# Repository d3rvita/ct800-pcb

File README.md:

# CT800-PCB

In order to become familiar with KiCAD and making something useful at the same time I started this project. The goal was to develop a PCB for the CT800 to ease the build-up. The CT800 is a dedicated chess computer made by Rasmus Althoff. It is very well documented, take a look at its homepage [www.ct800.net](https://www.ct800.net "CT800 Homepage") for detailed info. 

The developed PCB consists entirely of THT components except one SMD transistor, due to better availability of 3.3V logic level devices. Soldering SMD parts isn’t easy especially packages like LQFP64 with 0.5mm pitch, therefore the Olimex board was kept in this design. The CT800 was extended by some interfaces (RS232, Bluetooth, WLAN) for future use. The power supply was amended a bit too.

CAD files of appropriate panels for housings are also included in this project. There are two versions:

* the Spartan one consists of front and back panel which are bolted to the PCB by studs
* the Classic one consists of just a front panel for the housing used by Rasmus (Axxatronic BIM1006-BLK/PG or BIM1006-GY/PG)

These panels are intended to be transparent, hence there are no holes for display and LEDs. Due to transparency there is no need for additional button labels.

## Project Data

* __CT800_PCB__ directory contains the KiCAD project including project specific libs and footprints as well gerber files for PCB production

* __CT800_PANEL__ directory contains panels (in KiCAD layout and SVG formats) for different housings

* __gen_panel_acrylic.py__ Python script for generating panel layouts from PCB layout

* __bom.txt__ lists the bill of material, mounting material for panels not included (M3x8mm / M3x25mm studs, washers, bolts...)

## Power Supply

Depending on assembly the CT800 can be powered by different sources: 

* by a 5V source on the USB-A connector 
* by power adopter or external battery on the barrel jack
	* 8-12VDC if the 7805 voltage regulator is used 
	* 4-12VDC if the Pololu S9V11F5 is used
* by internal battery if a switch is used

The USB-B connector on the Olimex board is not intended for powering the CT800 but for USB devices like a sensor chessboard. So __don’t feed the CT800 via USB-B connector.__

__Don’t provide power from multiple sources simultaneously to the CT800 in general. This could lead to side effects or even damage!__

In order to feed the CT800 by low voltage power supply down to 4VDC  (e.g. battery) equip the PCB with the Pololu S9V11F5 voltage regulator (or similar 5V buck/boost converter) instead of the 7805. In this context replacing the 1N4007 diode by a Schottky type (e.g. 1N5818, SB130) is recommended for higher efficiency.

The CT800 firmware provides voltage monitoring for four NiMH (or alkaline) cells connected in serial, in order to protect rechargeable batteries from deep discharge. This only makes sense in conjunction with the Pololu regulator. Dispense with this monitoring eases the build-up, so omit it unless you really need it. To do so, omit the voltage divider components (R2, R3 and C1), instead connect the R2 pad next to C1 to 3.3V (red wire on ct800_spartan_bottom.jpg).

A power switch is not provided on the PCB but can be connected easily to PWR and USB_SEL pads.

### Operating Without Power Switch

The CT800 is immediately powered by plugging a 5V supply to the USB-A connector or a “wide range” power source to the barrel jack (8-12VDC or 4-12VDC depending on the used 5V regulator).

If battery monitoring is active (thus the Pololu is used), the USB power has to be redirected to 5V regulator’s input via the USB_SEL jumper: disrupt the connection on top side between the upper two pads and short-circuit the lower two. Otherwise powering via USB will result in “low batteries” error message. Because of this redirection the power adopter (or battery) is directly connected to the USB power supply. __Despite the fuses, this easily lead to damage in case two power sources are used simultaneously!__ Therefore use a switch instead or dispense with battery monitoring.

### Operating With Power Switch

Without battery monitoring a 2x3 pin toggle switch is sufficient to switch between USB-A and barrel jack supply. An external battery can still be used on the barrel jack. If internal battery is desired a 1x4 rotary switch is recommended for supply selection. Wire the switch as shown in the picture below, don’t forget to disrupt the red marked traces on the PCB.

Many other switch configurations are possible. Whatever you choose, ensure power sources are never short circuit!

## PCB Assembly

Read the entire text before starting assembly. Decide what power source you want to use for feeding the CT800 and if you need a power switch or not. Since the ESP-01 is not used yet by the firmware, there is no need for equipping it. This just leads to higher current consumption. It is recommended to place the smallest components first: the SMD transistor, resistors, capacitors and then the remaining parts but the display and Olimex board. Consider the polarity of diodes, LEDs (cathode to rectangular pad = ground) and polarized capacitors. Apply heat paste to the voltage regulator(s) and screw them to the PCB before soldering. If battery monitoring is used, activate the JP3 jumper on top side. Before placing display and Olimex board check the 5V and 3.3V voltages (there are test points on the PCB). __Don’t proceed until these voltages are alright.__ Before soldering the display, screw it to the PCB and adjust the height by putting washers in between. On some displays the polarity of the back light has to be changed. On the back side of the display are jumpers for this purpose, regard the data sheet. __Don’t solder the Olimex board to the PCB, use female header instead.__ For UART communication between µC and ESP-01 the resistor R27 on the Olimex board has to be removed. In order to prevent the gold-cap to be drained in off state, the VBAT jumper on the STM32H405 board has to be disrupted. 

## Schematic

## PCB

## Spartan Housing

## Classic Housing

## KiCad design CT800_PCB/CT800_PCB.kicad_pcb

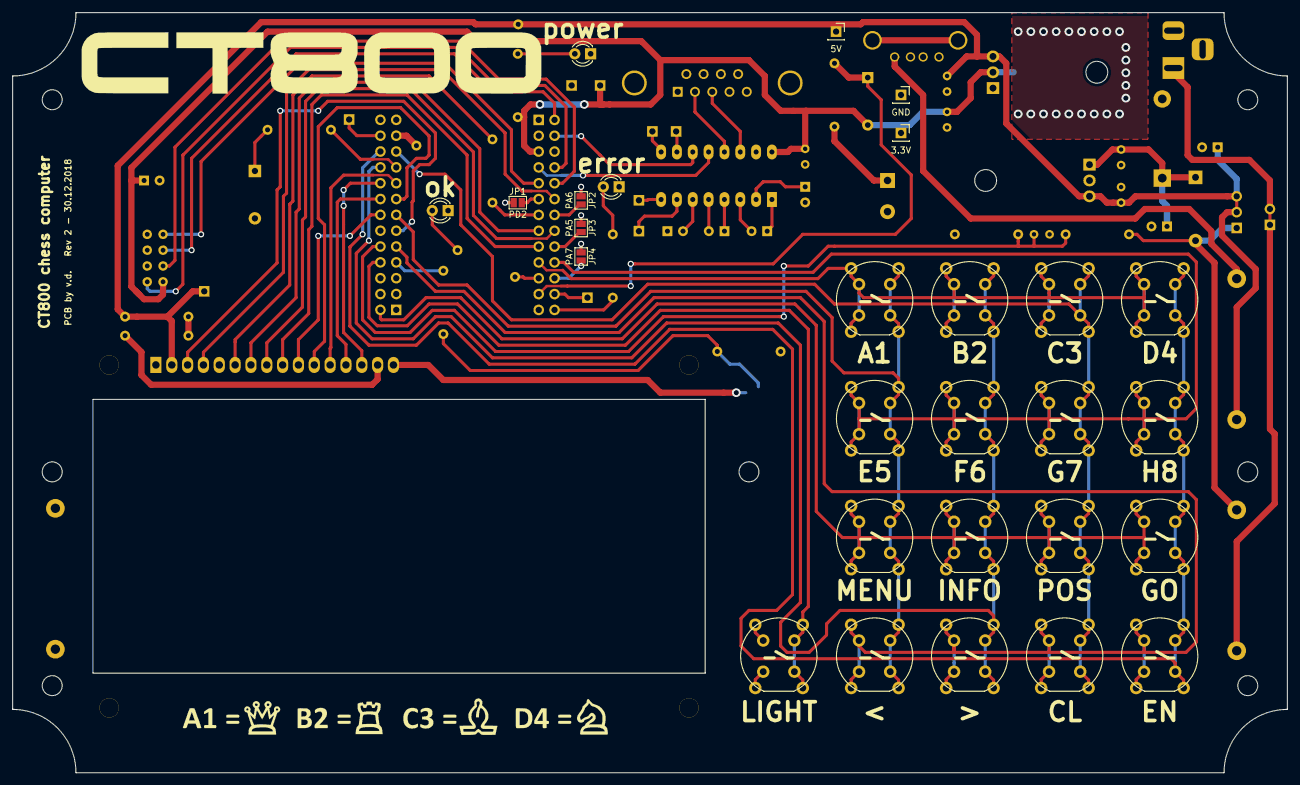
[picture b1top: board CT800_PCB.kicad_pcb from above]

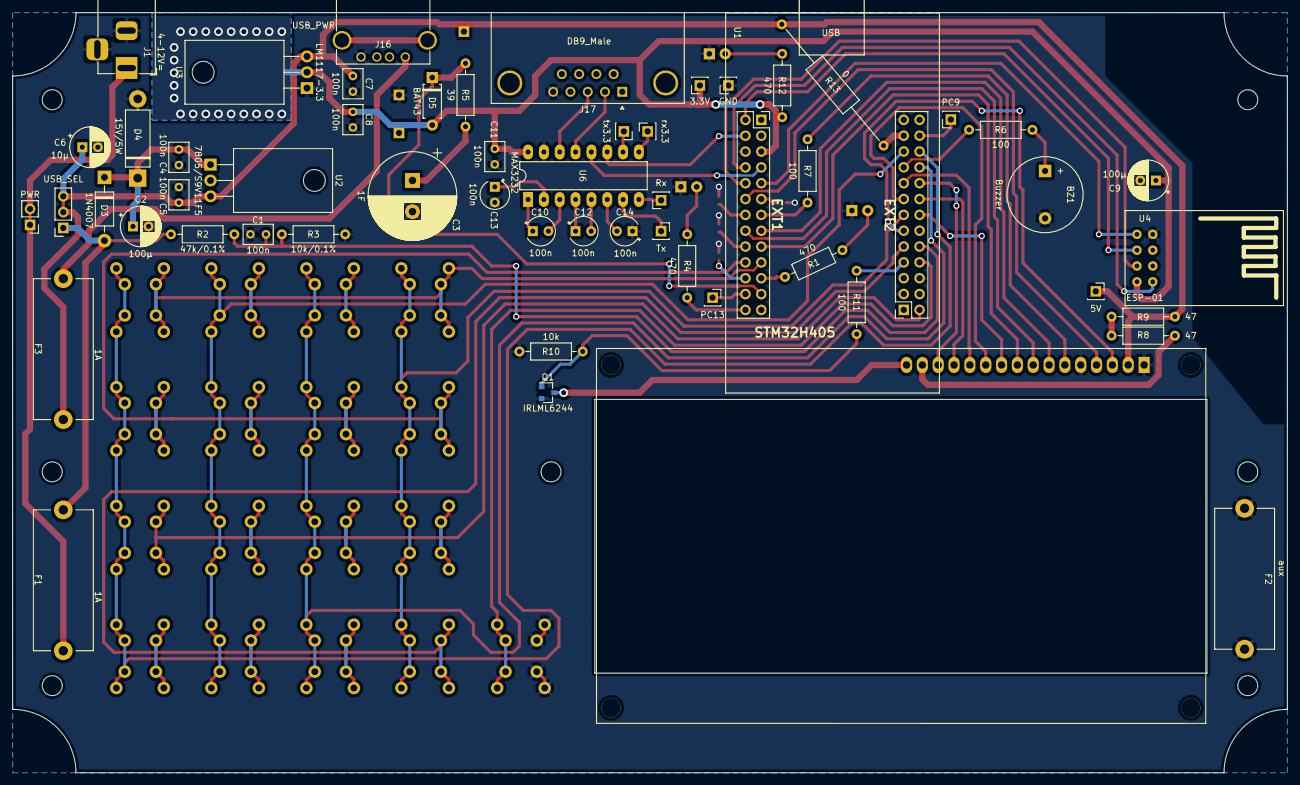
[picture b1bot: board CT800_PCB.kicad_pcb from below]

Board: 2 copper layers, 204.5 x 121.9 mm, 91 parts (54 on the bottom side), 68 nets.

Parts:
BZ1: Buzzer; Buzzer_12x9.5RM7.6
C1, C4, C5, C7, C8, C11: 100n; C_Rect_L4.6mm_W3.0mm_P2.50mm_MKS02_FKP02
C2, C9: 100µ; CP_Radial_D6.3mm_P2.50mm
C3: 1F; CP_Radial_D14.0mm_P5.00mm
C6: 10µ; CP_Radial_D6.3mm_P2.50mm
C10, C12, C13, C14: 100n; CP_Radial_Tantal_D4.5mm_P2.50mm
D1: ok; LED_D3.0mm
D2: error; LED_D3.0mm
D3: 1N4007; D_DO-41_SOD81_P10.16mm_Horizontal
D4: 15V/5W; D_5W_P12.70mm_Horizontal
D5: BAT43; D_A-405_P7.62mm_Horizontal
D6: power; LED_D3.0mm
F1, F3: 1A; Fuseholder_Cylinder-5x20mm_Stelvio-Kontek_PTF78_Horizontal_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
F2: aux; Fuseholder_Cylinder-5x20mm_Stelvio-Kontek_PTF78_Horizontal_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
H1, H2, H3, H4, H5, H6, H7: MountingHole; MountingHole_3.2mm_M3
J1: 4-12V=; BarrelJack_Horizontal
J2: PWR; Pin_Header_Straight_1x02_Pitch2.54mm
J3: PC13; PinSocket_1x01_P2.54mm_Vertical
J4: PC9; PinSocket_1x01_P2.54mm_Vertical
J6, J7: 5V; PinSocket_1x01_P2.54mm_Vertical
J8, J9: 3.3V; PinSocket_1x01_P2.54mm_Vertical
J10, J11: GND; PinSocket_1x01_P2.54mm_Vertical
J12: tx3.3; PinSocket_1x01_P2.54mm_Vertical
J13: rx3.3; PinSocket_1x01_P2.54mm_Vertical
J14: Tx; PinSocket_1x01_P2.54mm_Vertical
J15: Rx; PinSocket_1x01_P2.54mm_Vertical
J16: USB_PWR; USB_A
J17: DB9_Male; DSUB-9_Male_Horizontal_P2.77x2.84mm_EdgePinOffset9.90mm_Hou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
JP1: PD2; SolderJumper-2_P1.3mm_Open_Pad1.0x1.5mm
JP2: PA6; SolderJumper-2_P1.3mm_Open_Pad1.0x1.5mm
JP3: PA5; SolderJumper-2_P1.3mm_Open_Pad1.0x1.5mm
JP4: PA7; SolderJumper-2_P1.3mm_Open_Pad1.0x1.5mm
JP5: USB_SEL; PinSocket_1x03_P2.54mm_Vertical
Q1: IRLML6244; SOT-23
R1, R4, R12: 470; R_Axial_DIN0207_L6.3mm_D2.5mm_P10.16mm_Horizontal
R2: 47k/0.1%; R_Axial_DIN0207_L6.3mm_D2.5mm_P10.16mm_Horizontal
R3: 10k/0.1%; R_Axial_DIN0207_L6.3mm_D2.5mm_P10.16mm_Horizontal
R5: 39; R_Axial_DIN0207_L6.3mm_D2.5mm_P10.16mm_Horizontal
R6, R7, R11: 100; R_Axial_DIN0207_L6.3mm_D2.5mm_P10.16mm_Horizontal
R8, R9: 47; R_Axial_DIN0207_L6.3mm_D2.5mm_P10.16mm_Horizontal
R10: 10k; R_Axial_DIN0207_L6.3mm_D2.5mm_P10.16mm_Horizontal
R13: 0; R_Axial_DIN0309_L9.0mm_D3.2mm_P25.40mm_Horizontal
SW1: LIGHT; D6_3FTH
SW2: A1; D6_3FTH
SW3: E5; D6_3FTH
SW4: MENU; D6_3FTH
SW5: <; D6_3FTH
SW6: B2; D6_3FTH
SW7: F6; D6_3FTH
SW8: INFO; D6_3FTH
SW9: >; D6_3FTH
SW10: C3; D6_3FTH
SW11: G7; D6_3FTH
SW12: POS; D6_3FTH
SW13: CL; D6_3FTH
SW14: D4; D6_3FTH
SW15: H8; D6_3FTH
SW16: GO; D6_3FTH
SW17: EN; D6_3FTH
SYM1: CT800 Logo; ct800
SYM2: Promotion; promotion
U1: STM32H405; Olimex_STM32H405
U2: 7805/S9V11F5; TO-220-3_Horizontal_TabDown
U3: LM1117-3.3; TO-220-3_Horizontal_TabDown
U4: ESP-01
U5: DISP_4x20; LCD04x20BL
U6: MAX3232; DIP-16_W7.62mm_LongPads

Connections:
+3V3: C8.1, C9.1, C11.1, D5.2, J8.1, J9.1, R12.2, U1.5, U3.2, U4.8, U6.16
+5V: C5.1, C6.1, C7.1, F3.2, J6.1, J7.1, JP5.2, JP5.3, R9.2, R13.2, U2.3, U3.3, U5.2
+BATT: D3.2, F1.1, JP5.1, R2.1
ADC_BATT: C1.1, R2.2, R3.1, U1.36
DISP_D0: U1.15, U5.7
DISP_D1: U1.16, U5.8
DISP_D2: U1.17, U5.9
DISP_D3: U1.40, U5.10
DISP_D4: U1.41, U5.11
DISP_D5: U1.43, U5.12
DISP_D6: U1.42, U5.13
DISP_D7: U1.44, U5.14
DISP_EN: R7.2, U1.13
DISP_RS: U1.12, U5.4
DISP_V0: U1.37, U5.3
ESP_EN: U1.2, U4.6
ESP_RST: U1.10, U4.7
GND: BZ1.2, C1.2, C2.2, C3.2, C4.2, C5.2, C6.2, C7.2, C8.2, C9.2, C11.2, C13.2, C14.1, D1.1, D2.1, D4.2, D6.1, F2.1, F2.2, J1.2, J1.3, J10.1, J11.1, J16.4, J17.5, JP1.1, JP2.1, JP3.1, JP4.1, Q1.2, R3.2, R10.2, SW1.1, U1.6, U1.29, U1.32, U1.51, U2.2, U3.1, U4.1, U5.1, U5.5, U6.15
KEY_COL_1: SW2.2, SW3.2, SW4.2, SW5.2, U1.39
KEY_COL_2: SW6.2, SW7.2, SW8.2, SW9.2, U1.46
KEY_COL_3: SW10.2, SW11.2, SW12.2, SW13.2, U1.47
KEY_COL_4: SW14.2, SW15.2, SW16.2, SW17.2, U1.48
KEY_ROW_1: SW2.1, SW6.1, SW10.1, SW14.1, U1.19
KEY_ROW_2: SW3.1, SW7.1, SW11.1, SW15.1, U1.20
KEY_ROW_3: SW4.1, SW8.1, SW12.1, SW16.1, U1.28
KEY_ROW_4: SW5.1, SW9.1, SW13.1, SW17.1, U1.35
LCMD: R11.1, U1.33
LED_ERR: R4.2, U1.26
LED_OK: R1.2, U1.21
unnamed: BZ1.1, R6.2
unnamed: C2.1, C4.1, D3.1, D4.1, U2.1
unnamed: C3.1, R5.2
unnamed: C10.1, U6.1
unnamed: C10.2, U6.3
unnamed: C12.1, U6.4
unnamed: C12.2, U6.5
unnamed: C13.1, U6.2
unnamed: C14.2, U6.6
unnamed: D1.2, R1.1
unnamed: D2.2, R4.1
unnamed: D6.2, R12.1
unnamed: F1.2, J1.1, J2.1, J2.2
unnamed: F3.1, J16.1
unnamed: J3.1, U1.24
unnamed: J4.1, U1.50
unnamed: J12.1, U6.10
unnamed: J13.1, U6.9
unnamed: J14.1, U6.7
unnamed: J15.1, U6.8
unnamed: J17.2, U6.13
unnamed: J17.3, U6.14
unnamed: JP1.2, U1.11
unnamed: JP2.2, U1.14
unnamed: JP3.2, U1.18
unnamed: JP4.2, U1.22
unnamed: Q1.1, R10.1, R11.2
unnamed: Q1.3, U5.16
unnamed: R6.1, U1.45
unnamed: R7.1, U5.6
unnamed: R8.1, U5.15
unnamed: R8.2, R9.1
unnamed: R13.1, U1.49
unnamed: SW1.2, U1.34
UART1_RX: U1.7, U6.12
UART1_TX: U1.4, U6.11
UART3_RX: U1.9, U4.5
UART3_TX: U1.8, U4.4
VBAT: D5.1, R5.1, U1.23

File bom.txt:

Reference		 Quantity		 Value			 Description
BZ1 				1			"Buzzer"		"Buzzer/Beeper, not a bare piezo element"
C10 C12 C13 C14 	4			"100n/16V"		"Capacitor, D4.5mm P2.50mm"
C2 C9 				2			"100µ/16V"		"Capacitor, D6.3mm P2.50mm"
C3 					1			"1F/5.5V"		"Capacitor, D14.0mm P5.00mm"
C4 C7 C5 C11 C8 C1 	6			"100n/16V"		"Capacitor, L4.6mm W3.0mm P2.50mm"
C6 					1			"10µ/16V"		"Capacitor, D6.3mm P2.50mm"
D1 					1			"ok"			"LED D3.0mm green"
D2 					1			"error"			"LED D3.0mm red"
D6 					1			"power"			"LED D3.0mm green"
D3					1			"1N4007"		"Diode DO-41, alternatively a Schottky type"
D4 					1			"15V/5W"		"Diode D_5W"
D5 					1			"BAT43"			"Diode D_A-405"
F1 F2 F3 			2			"1A/fast"		"Fuseholder P22,5mm + Fuse 5x20mm"
J1 					1			"4-12V="		"BarrelJack (5.5mm / 2.1mm, plus inside)"
J16 				1			"USB_PWR"		"USB_A Connector"
J17 				1			"DB9_Male"		"DSUB-9_Male Connector P2.77x2.84mm (Offset_9.90mm_11.32mm)"
Q1 					1			"IRLML6244"		"MOSFET SOT-23"
R10 				1			"10k"			"Resistor 0204"
R13 				1			"0"				"Wire"
R2					1			"47k/0.1%"		"Resistor 0204, for battery monitoring only"
R3					1			"10k/0.1%"		"Resistor 0204, for battery monitoring only"
R4 R1 R12 			3			"470"			"Resistor 0204"
R5 					1			"39"			"Resistor 0204"
R6 R11 R7 			3			"100"			"Resistor 0204"
R9 R8 				2			"47"			"Resistor 0204, values depending on the display back light"
SW1 - SW17			17			"~"				"Switches, MULTIMEC 3FTH9 (10.16x7.62mm) or ITT DT6 (5x5mm)"
U1 					1			"STM32H405"		"Olimex STM32H405 Board, additional: 2pc. 2x13pin female header P2.54mm"
U2 					1			"7805/S9V11F5"	"5V Voltage Regulator TO220"
U3 					1			"LM1117-3.3"	"3.3V Voltage Regulator TO220"
U4 					1			"ESP-01"		"ESP8266 board"
U5					1			"DISP_4x20"		"4x20 Display based on ST7066, additional M2.5 bolts, nuts and washers for mounting"
U6 					1			"MAX3232"		"DIP-16_W7.62mm, socket recommended"

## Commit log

2019-01-23 typo
2019-01-24 ct800 url, VBAT jumper
2019-01-24 ESP-01 hint
2019-01-24 schematic pdf
